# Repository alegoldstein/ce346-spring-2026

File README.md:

# Electronic Game Table
# ce346-spring-2026

Firmware and PCB design for COMP_ENG 346: Microcontroller System Design.

For this project my group created an electronic table that added animations and score tracking to the common college games of beer pong and beer die.

To do so, we CNC'd a wooden table with channels to pour epoxy and placed ~800 WS2812B LEDs. Each half of the table had its own PCB (which are identical) which was responsible for monitoring the game state and controlling the LEDs accordingly using the FastLED library. Lastly, the power for this project was a large challenge because of the high current draw that WS2812B LEDs are capable of. To avoid overheating, we never had LEDs on at full brightness and avoided the color white as much as possible. The power source we used was capable of supplying 60A at 5V so monitoring shorts was also a high priority. We used bus bars that were suited for handling 60A and separated power and ground with large margins to avoid any accidental shorts. To ensure a uniform brightness level we added power injections to the LED strips with carefuly planned channels cut around in the available space left around the epoxy. 

<table align="center">
  <tr>
    <td align="center">
      <br>
      <em>The three of us pouring epoxy</em>
    </td>
    <td align="center">
      <br>
      <em>Fully assembled PCB</em>
    </td>
  </tr>
</table>

<table align="center">
  <tr>
    <td align="center">
      <br>
      <em>Inside of table while routing power and LEDs</em>
    </td>
    <td align="center">
      <br>
      <em>Setting up for demo, LED ring on where cup is placed</em>
    </td>
  </tr>
</table>

I hand wrote the game state code in C for an NRF52833 chip (found in NRF->software->apps->rave_rack) that used a 16 bit variable where bits 0-11 each represented 1 of the 12 cups on a half of a board (10 for pong and 2 for die). The NRF chip was also responsible for cycling through an 16 channel analog multiplexer used to check the values of IR sensors placed beneath each cup to determine whether they had been picked up or not. This information can be used to update the game state and infer the score (more cups missing means other teams score goes up). The NRF chip then communicates the game state to an ESP32 which was responsible for controlling the LEDs.

I also wrote C++ code for the ESP32 to animate the LEDs in response to game state changes. For example, during initialization the LEDs would snake around the border to indicate it was turned on and ready. If a cup was lifted (meaning someone scored) a celebration animation would occur. The FastLED library made this simpler since all that was needed was a buffer with each color and brightness we wanted each LED.

The reasoning for having 2 separate MCUs is due to the class being based on the NRF52833 chip, but our group running out of pins since we had a larger scope than expected for a 4 week project. 

https://github.com/user-attachments/assets/d65dbca0-1492-469c-94e2-22f77370f840

One half of the table featuring LED animations with epoxy cover on top

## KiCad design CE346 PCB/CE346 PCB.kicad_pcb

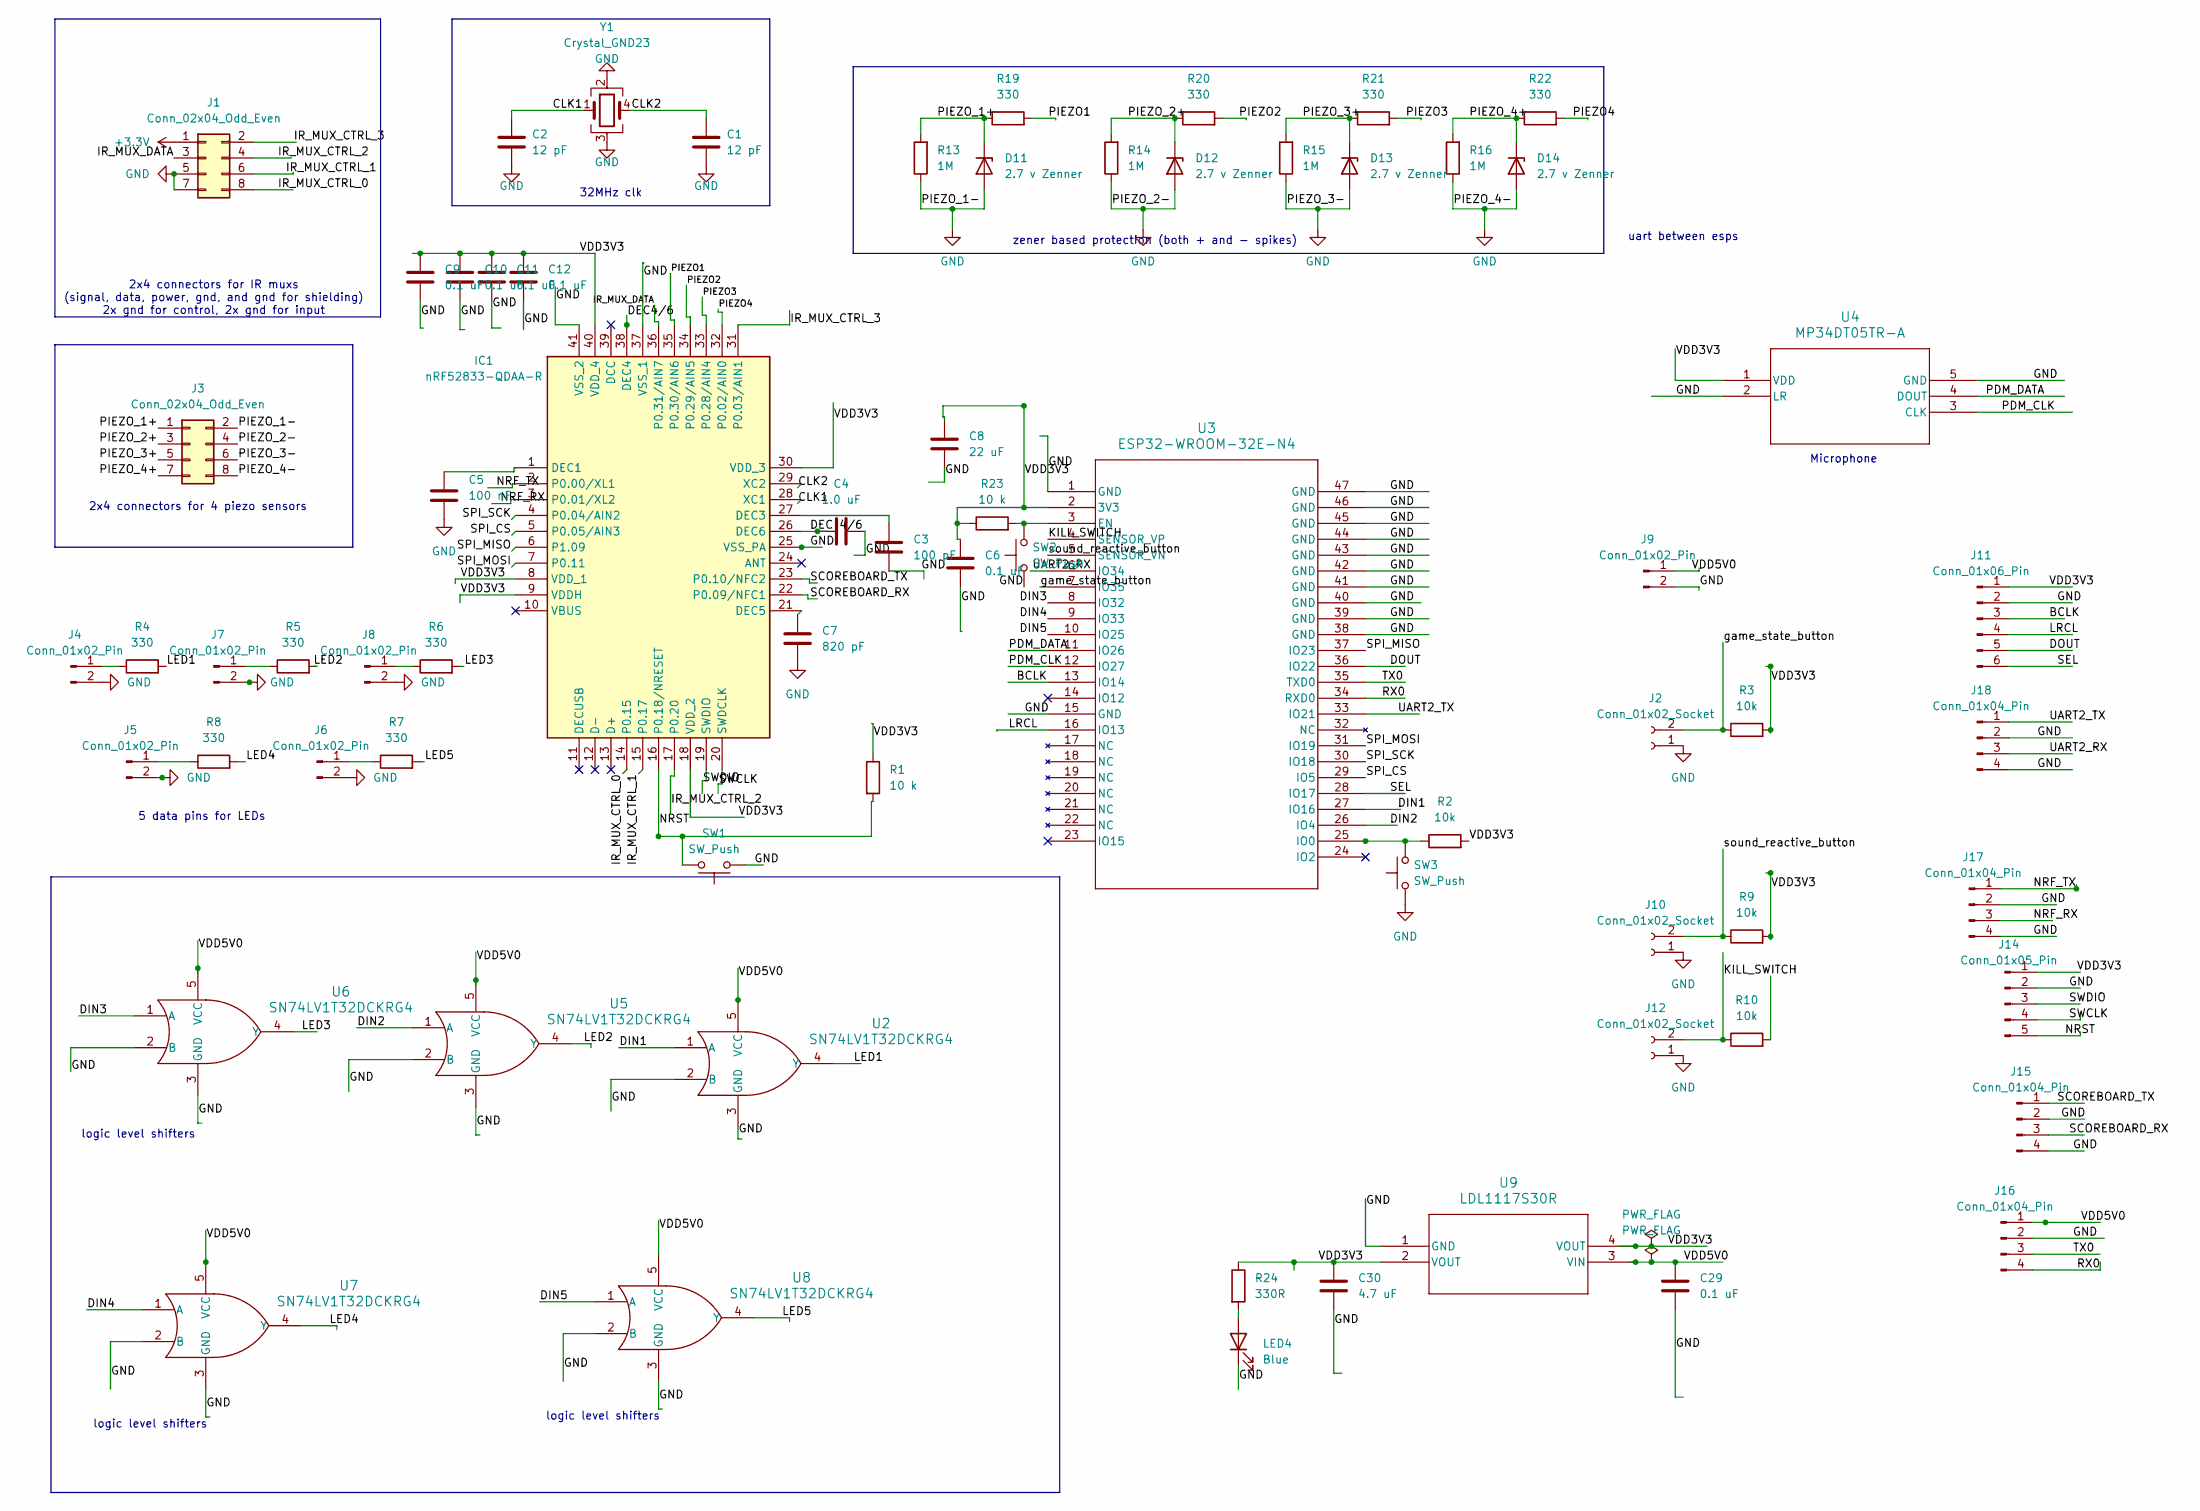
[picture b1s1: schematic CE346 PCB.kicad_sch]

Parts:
C1, C2: 12 pF; C_0402_1005Metric
C3: 100 pF; C_0402_1005Metric
C4: 1.0 uF; C_0402_1005Metric
C5: 100 nF; C_0402_1005Metric
C6, C9, C10, C11, C12, C29: 0.1 uF; C_0402_1005Metric
C7: 820 pF; C_0402_1005Metric
C8: 22 uF; C_0805_2012Metric
C30: 4.7 uF; C_0805_2012Metric
D11, D12, D13, D14: 2.7 v Zenner; D_SOD-123
IC1: nRF52833-QDAA-R; QFN40_5X5_DQ_NOR-L; Mouser Part Number 949-NRF52833-QDAA-R
J1, J3: Conn_02x04_Odd_Even; 2x4 jst
J2, J10, J12: Conn_01x02_Socket; PinHeader_1x02_P2.54mm_Vertical
J4, J5, J6, J7, J8, J9: Conn_01x02_Pin; PinHeader_1x02_P2.54mm_Vertical
J11: Conn_01x06_Pin; PinHeader_1x06_P2.54mm_Vertical
J14: Conn_01x05_Pin; PinHeader_1x05_P2.54mm_Vertical
J15, J16, J17, J18: Conn_01x04_Pin; PinHeader_1x04_P2.54mm_Vertical
LED4: Blue; LED_0603_1608Metric
R1, R23: 10 k; R_0805_2012Metric
R2, R3, R9, R10: 10k; R_0805_2012Metric
R4, R5, R6, R7, R8, R19, R20, R21, R22: 330; R_0805_2012Metric
R13, R14, R15, R16: 1M; R_0805_2012Metric
R24: 330R; C_0402_1005Metric
SW1, SW2, SW3: SW_Push; pushbutton
U2, U5, U6, U7, U8: SN74LV1T32DCKRG4; DBV0005A_N
U3: ESP32-WROOM-32E-N4; ESP32­WROOM­32E_EXP
U4: MP34DT05TR-A; MP34DT05TR-A_STM
U9: LDL1117S30R; SOT223_STM
Y1: Crystal_GND23; 32MHz Crystal

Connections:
+3.3V: J1.1
/BCLK: J11.3, U3.13 (IO14)
/CLK1: C2.1, IC1.28 (XC1), Y1.1
/CLK2: C1.1, IC1.29 (XC2), Y1.4
/DIN1: U2.1 (A), U3.27 (IO16)
/DIN2: U3.26 (IO4), U5.1 (A)
/DIN3: U3.8 (IO32), U6.1 (A)
/DIN4: U3.9 (IO33), U7.1 (A)
/DIN5: U3.10 (IO25), U8.1 (A)
/DOUT: J11.5, U3.36 (IO22)
/IR_MUX_CTRL_0: IC1.14 (P0.15), J1.8
/IR_MUX_CTRL_1: IC1.15 (P0.17), J1.6
/IR_MUX_CTRL_2: IC1.17 (P0.20), J1.4
/IR_MUX_CTRL_3: IC1.31 (P0.03/AIN1), J1.2
/IR_MUX_DATA: IC1.36 (P0.31/AIN7), J1.3
/KILL_SWITCH: J12.2, R10.1, U3.4 (SENSOR_VP)
/LED1: R4.2, U2.4 (Y)
/LED2: R5.2, U5.4 (Y)
/LED3: R6.2, U6.4 (Y)
/LED4: R8.2, U7.4 (Y)
/LED5: R7.2, U8.4 (Y)
/LRCL: J11.4, U3.16 (IO13)
/NRF_RX: IC1.3 (P0.01/XL2), J17.3
/NRF_TX: IC1.2 (P0.00/XL1), J17.1
/NRST: IC1.16 (P0.18/NRESET), J14.5, R1.2, SW1.2
/PDM_CLK: U3.12 (IO27), U4.3 (CLK)
/PDM_DATA: U3.11 (IO26), U4.4 (DOUT)
/PIEZO1: IC1.35 (P0.30/AIN6), R19.2
/PIEZO2: IC1.34 (P0.29/AIN5), R20.2
/PIEZO3: IC1.33 (P0.28/AIN4), R21.2
/PIEZO4: IC1.32 (P0.02/AIN0), R22.2
/PIEZO_1+: D11.1 (K), J3.1, R13.2, R19.1
/PIEZO_2+: D12.1 (K), J3.3, R14.2, R20.1
/PIEZO_3+: D13.1 (K), J3.5, R15.2, R21.1
/PIEZO_4+: D14.1 (K), J3.7, R16.2, R22.1
/RX0: J16.4, U3.34 (RXD0)
/SCOREBOARD_RX: IC1.22 (P0.09/NFC1), J15.3
/SCOREBOARD_TX: IC1.23 (P0.10/NFC2), J15.1
/SEL: J11.6, U3.28 (IO17)
/SPI_CS: IC1.5 (P0.05/AIN3), U3.29 (IO5)
/SPI_MISO: IC1.6 (P1.09), U3.37 (IO23)
/SPI_MOSI: IC1.7 (P0.11), U3.31 (IO19)
/SPI_SCK: IC1.4 (P0.04/AIN2), U3.30 (IO18)
/SWCLK: IC1.20 (SWDCLK), J14.4
/SWDIO: IC1.19 (SWDIO), J14.3
/TX0: J16.3, U3.35 (TXD0)
/UART2_RX: J18.3, U3.6 (IO34)
/UART2_TX: J18.1, U3.33 (IO21)
/VDD3V3: C6.1, C8.1, C9.1, C10.1, C11.1, C12.1, C30.2, IC1.8 (VDD_1), IC1.9 (VDDH), IC1.18 (VDD_2), IC1.30 (VDD_3), IC1.40 (VDD_4), J11.1, J14.1, R1.1, R2.2, R3.2, R9.2, R23.1, R24.1, U3.2 (3V3), U4.1 (VDD), U9.2 (VOUT), U9.4 (VOUT)
/VDD5V0: C29.2, J9.1, J16.1, U2.5 (VCC), U5.5 (VCC), U6.5 (VCC), U7.5 (VCC), U8.5 (VCC), U9.3 (VIN)
/game_state_button: J2.2, R3.1, U3.7 (IO35)
/sound_reactive_button: J10.2, R9.1, U3.5 (SENSOR_VN)
GND: C1.2, C2.2, C3.2, C4.2, C5.2, C6.2, C7.2, C8.2, C9.2, C10.2, C11.2, C12.2, C29.1, C30.1, D11.2 (A), D12.2 (A), D13.2 (A), D14.2 (A), IC1.25 (VSS_PA), IC1.37 (VSS_1), IC1.41 (VSS_2), J1.5, J1.7, J2.1, J3.2, J3.4, J3.6, J3.8, J4.2, J5.2, J6.2, J7.2, J8.2, J9.2, J10.1, J11.2, J12.1, J14.2, J15.2, J15.4, J16.2, J17.2, J17.4, J18.2, J18.4, LED4.1 (K), R13.1, R14.1, R15.1, R16.1, SW1.1, SW2.1, SW3.1, U2.2 (B), U2.3 (GND), U3.1 (GND), U3.15 (GND), U3.38 (GND), U3.39 (GND), U3.40 (GND), U3.41 (GND), U3.42 (GND), U3.43 (GND), U3.44 (GND), U3.45 (GND), U3.46 (GND), U3.47 (GND), U4.2 (LR), U4.5 (GND), U5.2 (B), U5.3 (GND), U6.2 (B), U6.3 (GND), U7.2 (B), U7.3 (GND), U8.2 (B), U8.3 (GND), U9.1 (GND), Y1.2, Y1.3
unnamed: C5.1, IC1.1 (DEC1)
unnamed: C3.1, IC1.27 (DEC3)
unnamed: C7.1, IC1.21 (DEC5)
unnamed: J4.1, R4.1
unnamed: J5.1, R8.1
unnamed: J6.1, R7.1
unnamed: J7.1, R5.1
unnamed: J8.1, R6.1
unnamed: LED4.2 (A), R24.2
unnamed: R23.2, SW2.2, U3.3 (EN)
unnamed: R2.1, SW3.2, U3.25 (IO0)

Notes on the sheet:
Microphone
5 data pins for LEDs
32MHz clk
logic level shifters
zener based protection (both + and - spikes)
uart between esps
2x4 connectors for 4 piezo sensors
2x4 connectors for IR muxs (signal, data, power, gnd, and gnd for shielding) 2x gnd for control, 2x gnd for input

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
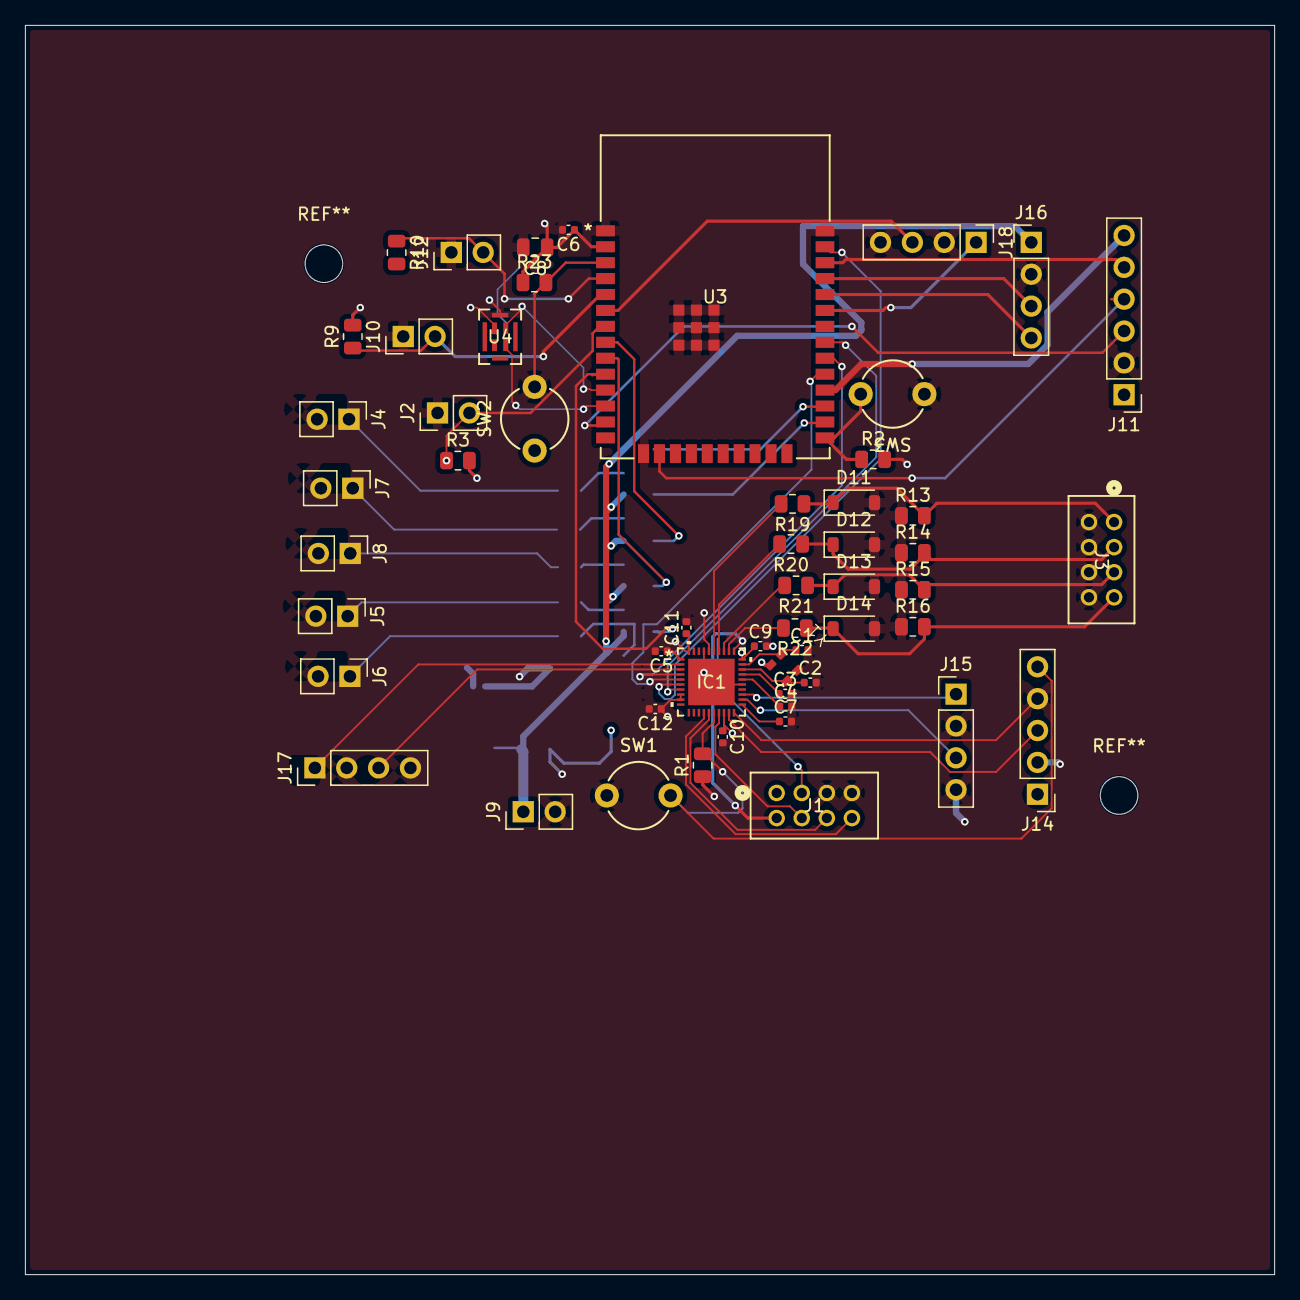
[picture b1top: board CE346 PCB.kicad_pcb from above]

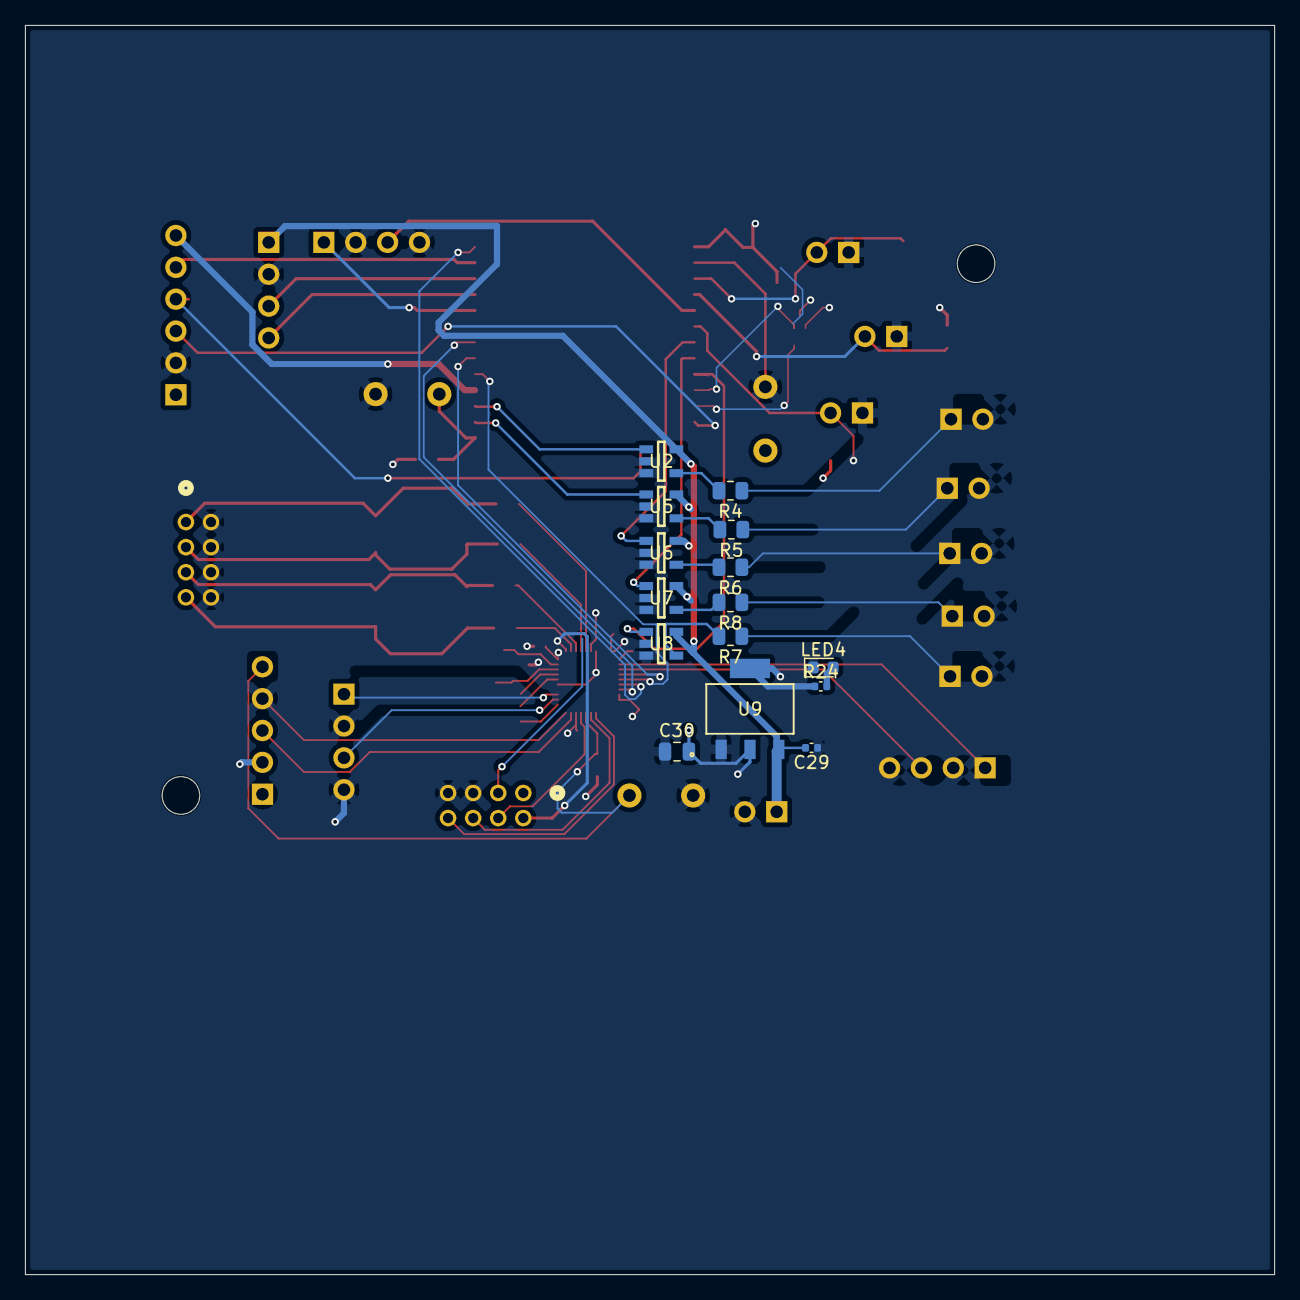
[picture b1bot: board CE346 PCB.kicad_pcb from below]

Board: 4 copper layers, 99.6 x 99.6 mm, 69 parts (15 on the bottom side), 64 nets.

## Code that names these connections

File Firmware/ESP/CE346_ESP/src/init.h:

//all pin definitinos except leds
#define PDM_DATA    26
#define PDM_CLK     27
#define BCLK        14
#define LRCL        13
#define SPI_MISO    23
#define SPI_MOSI    19
#define SPI_CS      5
#define SPI_SCK     18
#define DOUT        22
#define UART2_TX    21
#define UART2_RX    34
#define GAME_BTN    35
#define SOUND_BTN   39 //VN
#define KILL_BTN    36 //VP


void init_uart(void);

void init_spi(void);

void init_scoreboard();

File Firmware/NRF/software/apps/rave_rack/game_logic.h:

#include <stdint.h>
#include <stdio.h>

#include "app_timer.h"
#include "nrf_delay.h"
#include "nrf_gpio.h"
#include "nrfx_saadc.h"
#include "nrfx_spim.h"

//////////////////////////////////////////////
/// Pin definitions
//////////////////////////////////////////////

// IR sensor pins
#define IR_MUX_CTRL_0		NRF_GPIO_PIN_MAP(0, 15)
#define IR_MUX_CTRL_1		NRF_GPIO_PIN_MAP(0, 17)
#define IR_MUX_CTRL_2 		NRF_GPIO_PIN_MAP(0, 20)
#define IR_MUX_CTRL_3		NRF_GPIO_PIN_MAP(0, 3)
#define IR_MUX_DATA		NRF_SAADC_INPUT_AIN7
#define IR_THRESH		500				// Placeholder

// Piezoelectric sensor pins
#define PIEZO_1			NRF_SAADC_INPUT_AIN6
#define PIEZO_2			NRF_SAADC_INPUT_AIN5
#define PIEZO_3			NRF_SAADC_INPUT_AIN4
#define PIEZO_4			NRF_SAADC_INPUT_AIN0

// ADC channels
#define ADC_IR_CHANNEL		0
#define ADC_PIEZO_1_CHANNEL	1
#define ADC_PIEZO_2_CHANNEL	2
#define ADC_PIEZO_3_CHANNEL	3
#define ADC_PIEZO_4_CHANNEL	4

// SPI pins
#define SPI_CLK			NRF_GPIO_PIN_MAP(0, 4)
#define SPI_CS			NRF_GPIO_PIN_MAP(0, 5)
#define SPI_MISO		NRF_GPIO_PIN_MAP(1, 9)
#define SPI_MOSI		NRF_GPIO_PIN_MAP(0, 11)

// UART pins
#define SCOREBOARD_RX		NRF_GPIO_PIN_MAP(0, 9)
#define SCOREBOARD_TX		NRF_GPIO_PIN_MAP(0, 10)

// Reset pin
#define NRF_RESET		NRF_GPIO_PIN_MAP(0, 18)	

//////////////////////////////////////////////
/// Game logic
//////////////////////////////////////////////

typedef struct {
	uint8_t TEAM_1_SCORE; 		// Each table assumes its cups are TEAM_1_SCORE
	uint8_t TEAM_2_SCORE;
	bool PONG;
	bool DICE;
	uint8_t TEAM_1_NUM_CUPS;
	uint8_t TEAM_2_NUM_CUPS;
	// uint8_t MASTER_PCB;
} game_state_t;

// Function declarations
void init_game(game_state_t *game, nrfx_spim_t *spim_inst);

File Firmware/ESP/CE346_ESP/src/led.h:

#include <stdint.h>

//led count and data pin declarations
#define CHIPSET WS2812B
#define NUM_LEDS1   184 //left ch
#define NUM_LEDS2   184 //right ch
#define NUM_LEDS3   168 //cups
#define NUM_LEDS4   43  //logo
#define NUM_LEDS5   213 //border

#define DIN1    16
#define DIN2    4   
#define DIN3    32
#define DIN4    33
#define DIN5    25

#define BOTT_LEFT   0b11000000
#define BOTT_RIGHT  0b00110000
#define TOP_LEFT    0b00001100
#define TOP_RIGHT   0b00000011

//definitions for functions to control table leds
//init leds, flash around the table upon powering on
void led_init(void);

//light up quadrant based on piezo sensing
void led_quadrant(uint8_t corner);

//light up rings around cups based on uint8_t cups data in game stuct and game mode
void led_cups(uint16_t cup_array);

//light up leds reacting to sound
void led_sound(void);

//mini celebration when an opponent cup is lifted (you scored)
void led_cup_lift(void);

//celebratory light display for team when their oppponent loses
//at some point the ESPs need to determine which side theyre responsible for
void led_celebrate(void);

//turn off all leds
void led_kill(void);

void led_test(void);

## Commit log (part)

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2026-05-04 schematic work
2026-05-05 schem
2026-05-05 better schematic
2026-05-05 small changes
2026-05-08 scjemaitc
2026-05-19 Finally added all of these files so I won't lose them again
2026-05-19 updating the footprint and symbols libraries
2026-05-19 updating the footprint library again
2026-05-19 pushing the changes
2026-05-20 pushing the changes to the routed PCB
2026-05-29 initialize firmware
2026-05-29 try again
2026-05-29 Populated ESP folder
2026-05-29 Began Rave Rack firmware
2026-06-04 game flow work
2026-06-05 Added PCB testing code and copied nrf52x-base directory to enable flashing
2026-06-05 Reorganized directory hierarchy
2026-06-06 more esp code
2026-06-06 restore ESP rave rack files
2026-06-06 restore ESP CE346 code
2026-06-06 Testing code
2026-06-07 6/7 morning
2026-06-07 Firmware edits
2026-06-07 adc interrupts
2026-06-08 led test
2026-06-08 ed test debugging
2026-06-09 Updated comms code
2026-06-09 esp code for ir sensors
